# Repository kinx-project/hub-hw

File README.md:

This repository contains the hardware design files for the kinX USB hub, a
bus-powered 4-port (2 internal, 2 external) USB hub for use within the Kinesis
Advantage keyboard in combination with the kinX keyboard controller.

The kinX USB hub is based on the Cypress HX2VL series USB controller,
specifically the [Cypress
CY7C65632-48AXCT](http://www.cypress.com/part/cy7c65632-48axct).

The design has been created with the following resources:

* [CY7C65632-48AXCT datasheet](http://www.cypress.com/file/114101/download)
* [HX2VL: Guidelines on System Design](http://www.cypress.com/file/122726/download)
* [CY4607M (CY7C65632-48AXCT devboard) schematic and BOM](http://www.cypress.com/documentation/other-resources/reduced-bom-schematic-cy7c65642-family-hx2vl-usb-20-hub-controller)
* [Example schematic for the QFN28 version](http://www.cypress.com/file/117521/download)

You can order this PCB at [OSH Park](https://oshpark.com/shared_projects/0aJAMwpd).

You can order the components at [Digi-Key](https://www.digikey.ch/short/pm8417).

## See also

https://github.com/kinx-project/mk66f-blaster for writing the EEPROM.

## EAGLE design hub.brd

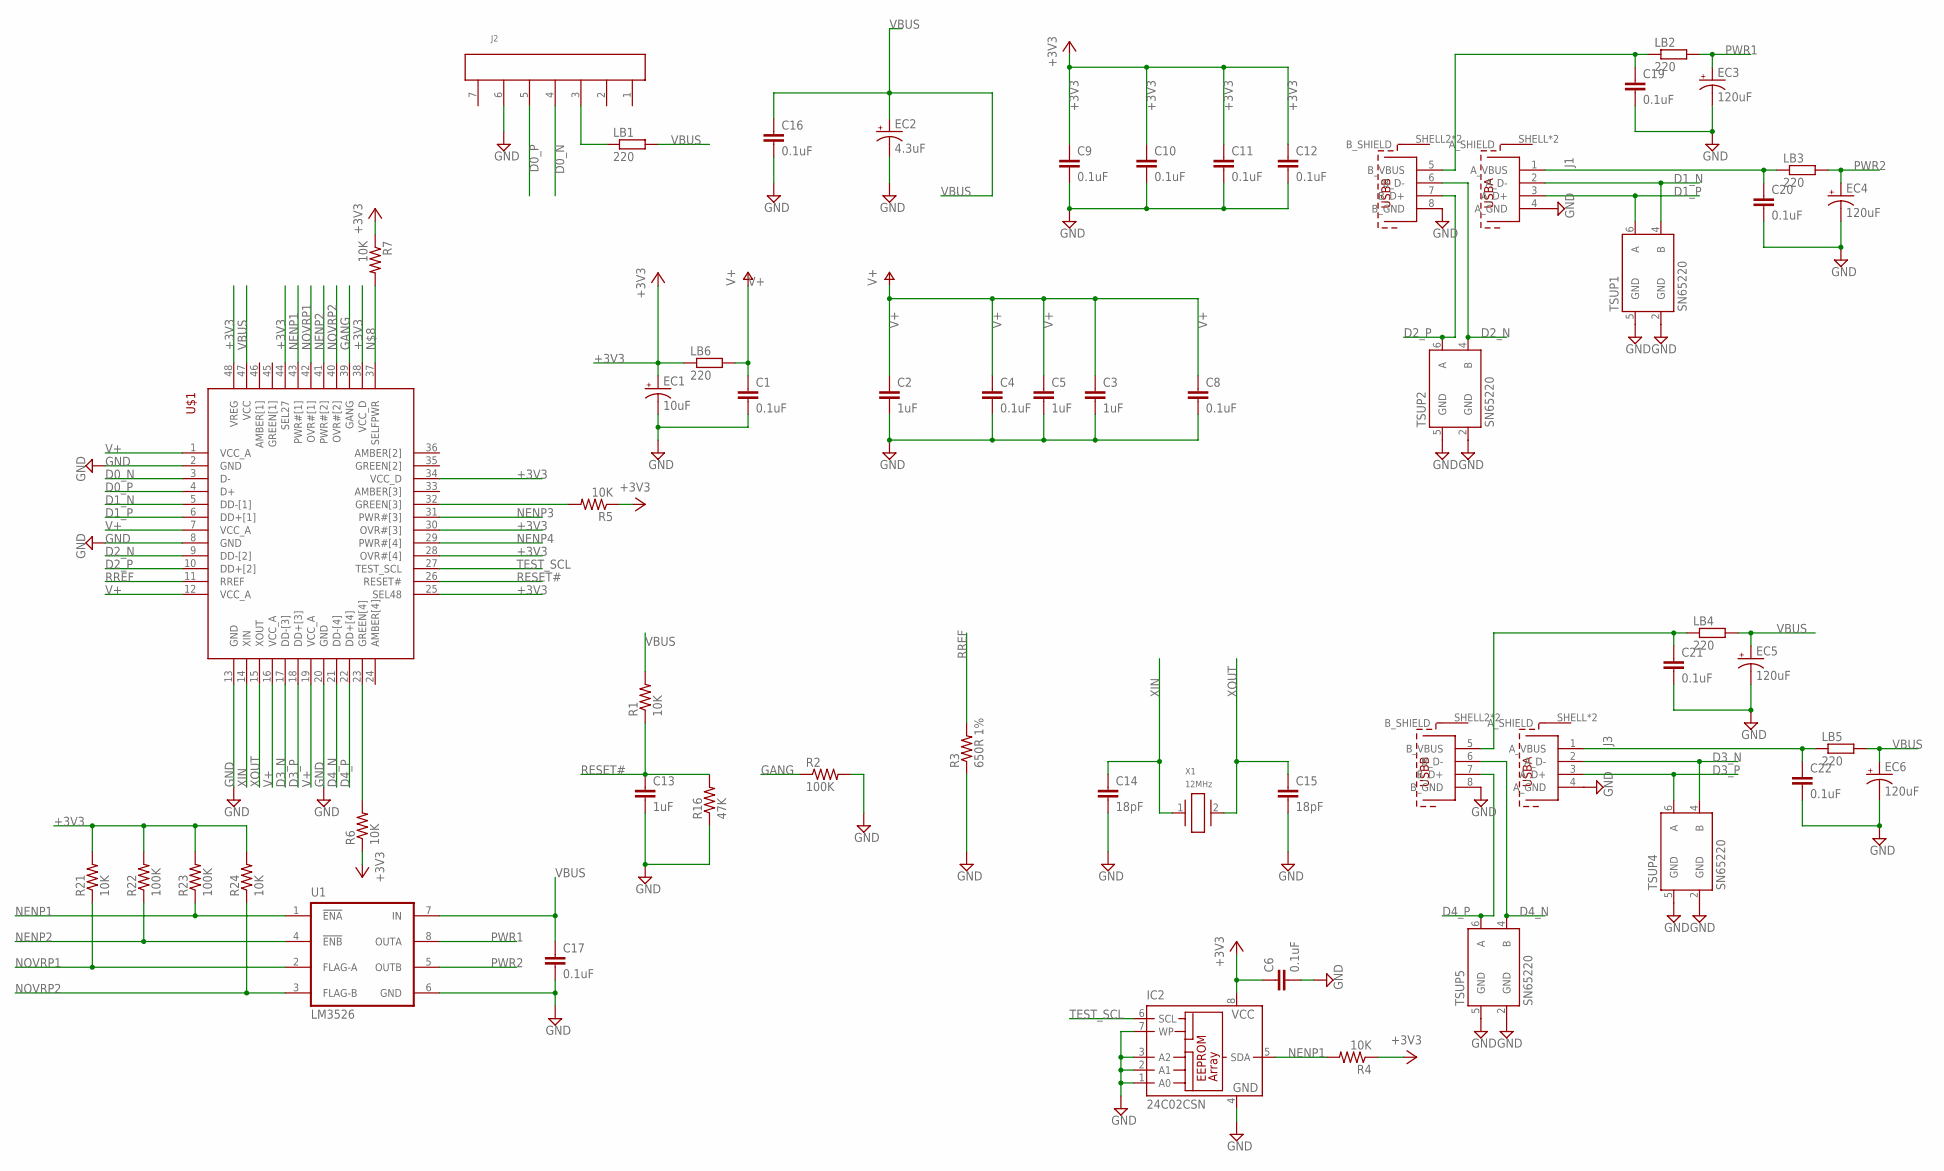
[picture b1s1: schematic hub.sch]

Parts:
C1, C4, C6, C8, C9, C10, C11, C12, C16, C17, C19, C20, C21, C22: 0.1uF; C0805; MPN GRM21BR71H104KA01L; DIGIKEY 732-8026-1-ND
C2, C3, C5, C13: 1uF; C0805; MPN C0805C105K4RACTU; DIGIKEY 399-1284-1-ND
C14, C15: 18pF; C0805; MPN CL21C180JBANNNC; DIGIKEY 1276-1107-1-ND
EC1: 10uF; CPOL-RADIAL-2.5MM-6.5MM; MPN UST1H100MDD1TE; DIGIKEY 493-16013-1-ND
EC2: 4.3uF; UD-5X5,8_NICHICON; MPN UUP1C4R7MCL1GS; DIGIKEY 338-3973-1-ND
EC3, EC4, EC5, EC6: 120uF; CPOL-RADIAL-2.5MM-6.5MM; MPN ELXY250ELL121MF15D; DIGIKEY 565-1791-ND
IC2: 24C02CSN; SO-08; DIGIKEY 24C02C/SN-ND
J1, J3: 61400826021; MPN 61400826021; DIGIKEY 732-2107-ND
J2: 62000711622; MPN 440054-7; DIGIKEY A100039-ND
LB1, LB2, LB3, LB4, LB5, LB6: 220; R0805; MPN BLM21PG221SN1D; DIGIKEY 490-1054-1-ND
R1, R4, R5, R6, R7, R21, R24: 10K; M0805; MPN RC0805FR-0710KL; DIGIKEY 311-10.0KCRCT-ND
R2, R22, R23: 100K; M0805; MPN RC0805FR-07100KL; DIGIKEY 311-100KCRCT-ND
R3: 650R 1%; M0805; MPN RC0805FR-07649RL; DIGIKEY 311-649CRCT-ND
R16: 47K; M0805; MPN RC0805FR-0747KL; DIGIKEY 311-47.0KCRCT-ND
TSUP1, TSUP2, TSUP4, TSUP5: SN65220; SOT23-6; MPN SN65220DBVR; DIGIKEY 296-9694-1-ND
U1: LM3526; SO08; MPN LM3526MX-L/NOPB; DIGIKEY LM3526MX-L/NOPBCT-ND
U$1: CY7C65632; TQFP48_7X7; MPN CY7C65632-48AXCT; DIGIKEY 428-3155-1-ND
X1: 12MHz; XTAL_ABLS2-24.000MHZ-D4YF-T; MPN ABLS-12.000MHZ-B2-T; DIGIKEY 535-9067-1-ND

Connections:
+3V3: C6.1, C9.1, C10.1, C11.1, C12.1, EC1.1 (+), IC2.8 (VCC), LB6.1, R4.1, R5.1, R6.1, R7.1, R21.2, R22.2, R23.2, R24.2, U$1.25 (SEL48), U$1.28 (OVR#[4]), U$1.30 (OVR#[3]), U$1.34 (VCC_D), U$1.38 (VCC_D), U$1.44 (SEL27), U$1.48 (VREG)
D0_N: J2.4, U$1.3 (D-)
D0_P: J2.5, U$1.4 (D+)
D1_N: J1.2 (A_D-), TSUP1.4 (B), U$1.5 (DD-[1])
D1_P: J1.3 (A_D+), TSUP1.6 (A), U$1.6 (DD+[1])
D2_N: J1.6 (B_D-), TSUP2.4 (B), U$1.9 (DD-[2])
D2_P: J1.7 (B_D+), TSUP2.6 (A), U$1.10 (DD+[2])
D3_N: J3.2 (A_D-), TSUP4.4 (B), U$1.17 (DD-[3])
D3_P: J3.3 (A_D+), TSUP4.6 (A), U$1.18 (DD+[3])
D4_N: J3.6 (B_D-), TSUP5.4 (B), U$1.21 (DD-[4])
D4_P: J3.7 (B_D+), TSUP5.6 (A), U$1.22 (DD+[4])
GANG: R2.1, U$1.39 (GANG)
GND: C1.2, C2.2, C3.2, C4.2, C5.2, C6.2, C8.2, C9.2, C10.2, C11.2, C12.2, C13.2, C14.2, C15.2, C16.2, C17.2, C19.2, C20.2, C21.2, C22.2, EC1.2 (-), EC2.-, EC3.2 (-), EC4.2 (-), EC5.2 (-), EC6.2 (-), IC2.1 (A0), IC2.2 (A1), IC2.3 (A2), IC2.4 (GND), IC2.7 (WP), J1.4 (A_GND), J1.8 (B_GND), J2.6, J3.4 (A_GND), J3.8 (B_GND), R2.2, R3.1, R16.1, TSUP1.2 (GND), TSUP1.5 (GND), TSUP2.2 (GND), TSUP2.5 (GND), TSUP4.2 (GND), TSUP4.5 (GND), TSUP5.2 (GND), TSUP5.5 (GND), U1.6 (GND), U$1.2 (GND), U$1.8 (GND), U$1.13 (GND), U$1.20 (GND)
unnamed: C19.1, J1.5 (B_VBUS), LB2.1
unnamed: C21.1, J3.5 (B_VBUS), LB4.1
unnamed: C22.1, J3.1 (A_VBUS), LB5.1
unnamed: C20.1, J1.1 (A_VBUS), LB3.1
unnamed: J2.3, LB1.1
unnamed: R6.2, U$1.23 (GREEN[4])
unnamed: R5.2, U$1.32 (GREEN[3])
unnamed: R7.2, U$1.37 (SELFPWR)
NENP1: IC2.5 (SDA), R4.2, R23.1, U1.1 (!ENA!), U$1.43 (PWR#[1])
NENP2: R22.1, U1.4 (!ENB!), U$1.41 (PWR#[2])
NENP3: U$1.31 (PWR#[3])
NENP4: U$1.29 (PWR#[4])
NOVRP1: R21.1, U1.2 (FLAG-A), U$1.42 (OVR#[1])
NOVRP2: R24.1, U1.3 (FLAG-B), U$1.40 (OVR#[2])
PWR1: EC3.1 (+), LB2.2, U1.8 (OUTA)
PWR2: EC4.1 (+), LB3.2, U1.5 (OUTB)
RESET#: C13.1, R1.1, R16.2, U$1.26 (RESET#)
RREF: R3.2, U$1.11 (RREF)
TEST_SCL: IC2.6 (SCL), U$1.27 (TEST_SCL)
V+: C1.1, C2.1, C3.1, C4.1, C5.1, C8.1, LB6.2, U$1.1 (VCC_A), U$1.7 (VCC_A), U$1.12 (VCC_A), U$1.16 (VCC_A), U$1.19 (VCC_A)
VBUS: C16.1, C17.1, EC2.+, EC5.1 (+), EC6.1 (+), LB1.2, LB4.2, LB5.2, R1.2, U1.7 (IN), U$1.47 (VCC)
XIN: C14.1, U$1.14 (XIN), X1.1
XOUT: C15.1, U$1.15 (XOUT), X1.2

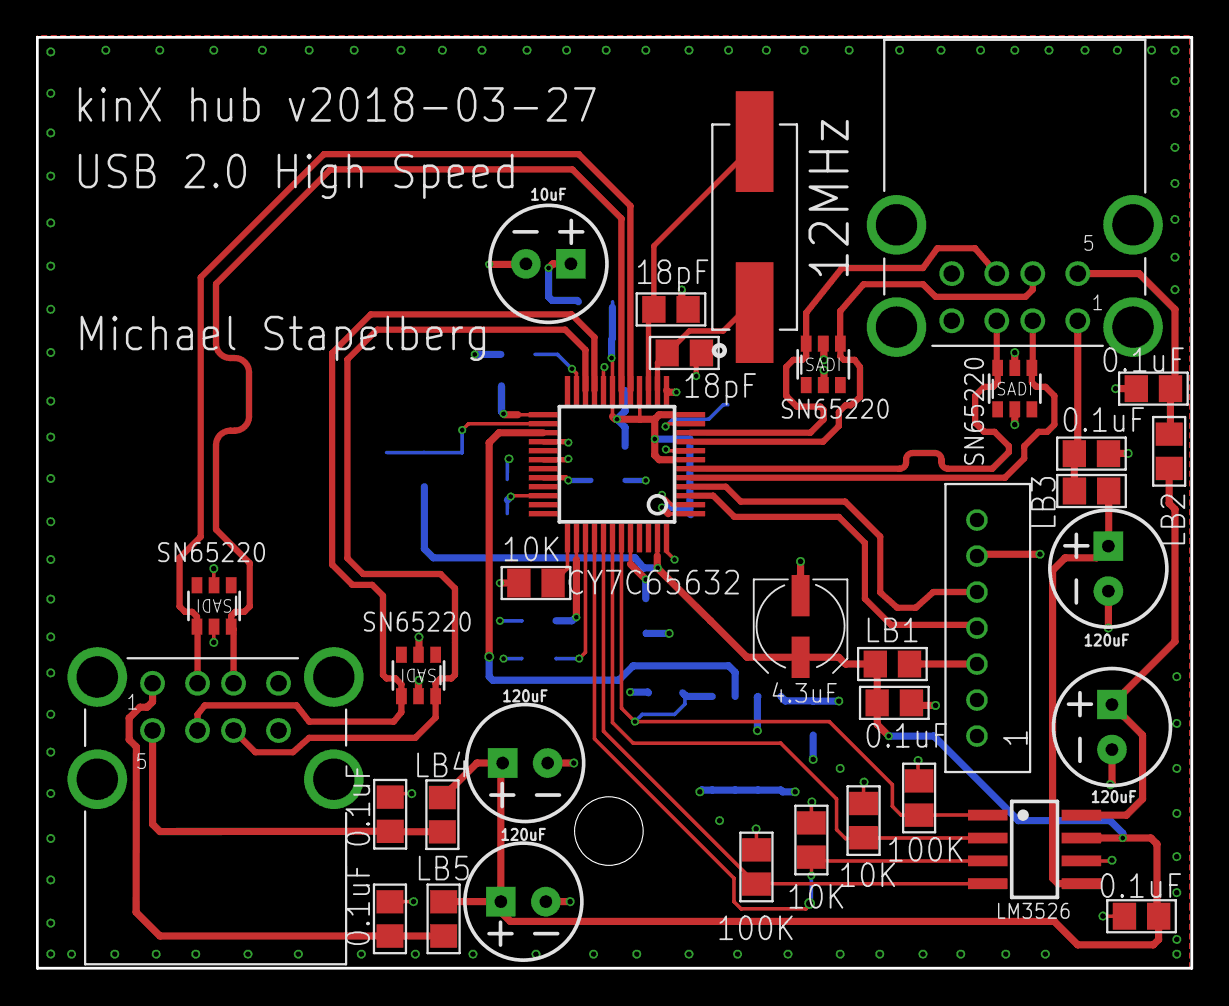
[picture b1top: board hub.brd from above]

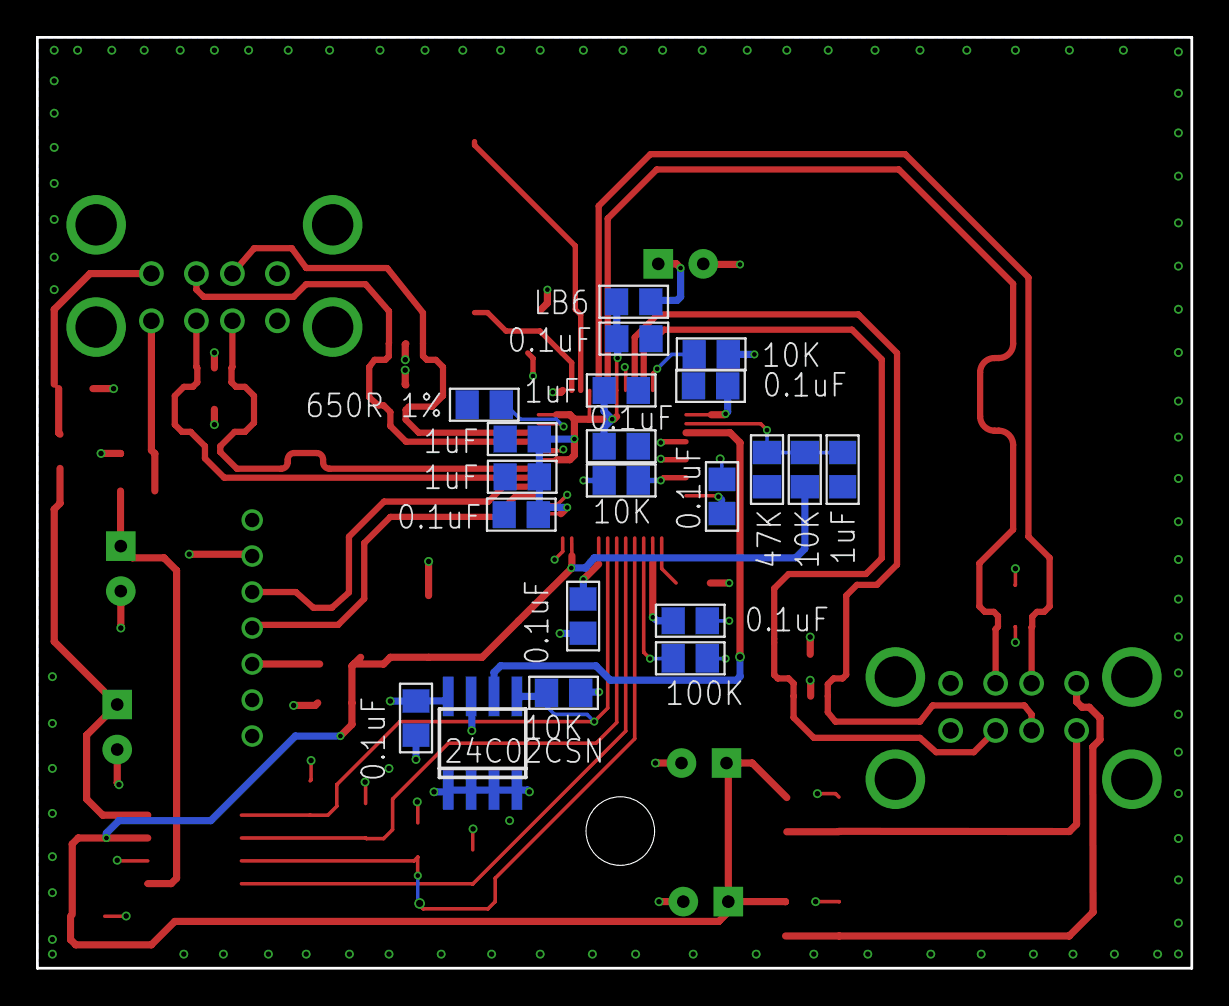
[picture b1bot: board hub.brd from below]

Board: 4 copper layers, 64.1 x 51.7 mm, 55 parts (21 on the bottom side), 34 nets.

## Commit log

2018-03-27 Add USB 2.0 High Speed hub schematic/board
    …as of 34c3.
2018-03-27 switch to crystal with correct drive level (supporting 600μW)
2018-03-27 finish silk screen
2018-03-27 give crystal more space
2018-03-27 BOM fix: swap 0603 649R for 0805
2018-03-27 pick ferrite beads
2018-03-27 move vias for DRC
2018-03-27 pick 18pF caps
2018-03-27 add and connect I2C EEPROM
2018-03-27 Switch to 0805 capacitors for consistency
2018-03-27 finish pin-strapping
2018-03-27 complete BOM
2018-03-27 silkscreen improvements
2018-03-27 update EC1 with same footprint as EC3-EC6
2018-03-27 silkscreen: better direction marking for SN65220
2018-03-27 fix EC1 silkscreen
2018-03-27 pick resistors
2018-03-27 Switch EC3, EC4, EC5, EC6 to ELXY250ELL121MF15D from vendor BOM
2018-03-27 pick wire-to-board connector
2018-03-27 add part outline to tPlace layer for R, C, L parts
    For a nicer silkscreen :)
2018-03-27 BOM fix: swap 0603 18pF caps for 0805
2018-03-27 pick capacitors
2018-03-27 re-route USB for oshpark PCBs
2018-03-27 enlarge drill holes for DRC
2018-03-27 pick USB transient suppressors
2018-03-27 pin-strap SELFPWR to +3V3 (bus-powered → self-powered)
2018-03-27 update silkscreen for new revision
2018-03-27 add eagle library files to git
2018-03-27 add BOM to git
2018-04-14 Change 0.1μF capacitors from 490-1666-1-ND to 732-8026-1-ND
    The former is no longer available.
2018-04-14 Rename bom to bom.digikey.csv for consistency with mk66f-hw
2018-04-14 add USB cables to BOM
2018-04-17 add OSH Park link
2018-04-17 Add Digi-Key link
2019-06-03 update digikey BOM

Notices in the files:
parts and their libraries:
InputOutputIO: Copyright: Würth Elektronik
national-semi: Copyright (C) 2008, Bob Starr
SparkFun-Capacitors: Licensing: Creative Commons ShareAlike 4.0 International - https://creativecommons.org/licenses/by-sa/4.0
